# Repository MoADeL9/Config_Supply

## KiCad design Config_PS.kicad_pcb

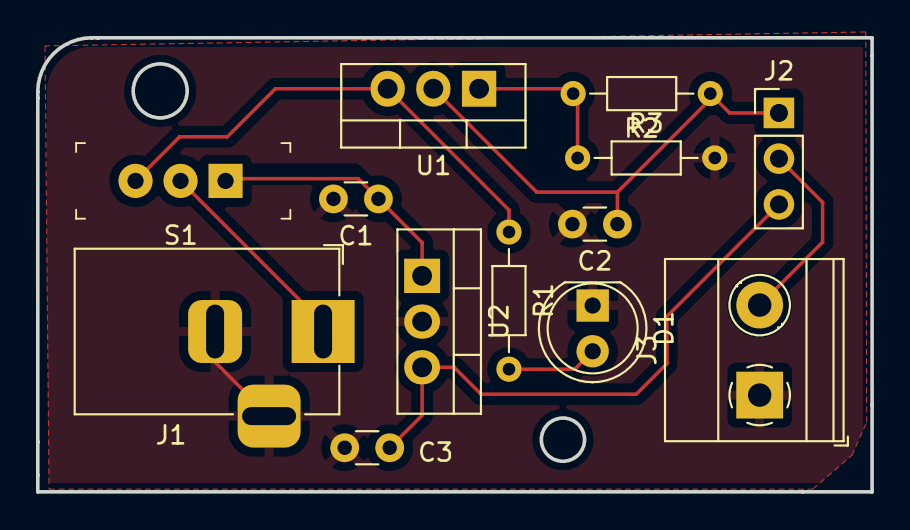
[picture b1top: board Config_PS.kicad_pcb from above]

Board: 2 copper layers, 46.3 x 25.2 mm, 13 parts (0 on the bottom side), 9 nets.

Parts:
C1: 10uf; C_Disc_D3.0mm_W1.6mm_P2.50mm
C2: 1uf; C_Disc_D3.0mm_W1.6mm_P2.50mm
C3: 0.1uf; C_Disc_D3.0mm_W1.6mm_P2.50mm
D1: LED; LED_D5.0mm
J1: Barrel_Jack_Switch; BarrelJack_Horizontal
J2: Conn_01x03_Pin; PinHeader_1x03_P2.54mm_Vertical
J3: Screw_Terminal_01x02; TerminalBlock_Phoenix_MKDS-1,5-2_1x02_P5.00mm_Horizontal
R1, R2: 330; R_Axial_DIN0204_L3.6mm_D1.6mm_P7.62mm_Horizontal
R3: 560; R_Axial_DIN0204_L3.6mm_D1.6mm_P7.62mm_Horizontal
S1: EG1218; Switch_Slide_11.6x4mm_EG1218
U1: LM317_TO-220; TO-220-3_Vertical
U2: LM7805_TO220; TO-220-3_Vertical

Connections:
/3.3V: C2.1, J2.1, R2.1, U1.2 (VO)
/5V: C3.1, J2.3, U2.3 (VO)
/PWR_input: J1.1, S1.2
/PWR_output: J2.2, J3.2
/VIN_3.3: R1.1, S1.3, U1.3 (VI)
/VIN_5: C1.1, S1.1, U2.1 (VI)
GND: C1.2, C2.2, C3.2, D1.1 (K), J1.2, J1.3, J3.1, R3.2, U2.2 (GND)
unnamed: D1.2 (A), R1.2
unnamed: R2.2, R3.1, U1.1 (ADJ)

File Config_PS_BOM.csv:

"Id";"Designator";"Footprint";"Quantity";"Designation";"Supplier and ref";
1;"U2";"TO-220-3_Vertical";1;"LM7805_TO220";;;
2;"C3";"C_Disc_D3.0mm_W1.6mm_P2.50mm";1;"0.1uf";;;
3;"J1";"BarrelJack_Horizontal";1;"Barrel_Jack_Switch";;;
4;"U1";"TO-220-3_Vertical";1;"LM317_TO-220";;;
5;"J2";"PinHeader_1x03_P2.54mm_Vertical";1;"Conn_01x03_Pin";;;
6;"S1";"Switch_Slide_11.6x4mm_EG1218";1;"EG1218";;;
7;"J3";"TerminalBlock_Phoenix_MKDS-1,5-2_1x02_P5.00mm_Horizontal";1;"Screw_Terminal_01x02";;;
8;"D1";"LED_D5.0mm";1;"LED";;;
9;"C2";"C_Disc_D3.0mm_W1.6mm_P2.50mm";1;"1uf";;;
10;"C1";"C_Disc_D3.0mm_W1.6mm_P2.50mm";1;"10uf";;;
11;"R3";"R_Axial_DIN0204_L3.6mm_D1.6mm_P7.62mm_Horizontal";1;"560";;;
12;"R2,R1";"R_Axial_DIN0204_L3.6mm_D1.6mm_P7.62mm_Horizontal";2;"330";;;

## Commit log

2025-05-17 git now tracks the files inside the config_supply
2025-05-17 deleted date in the schematic design
2025-05-17 added custom logo
2025-05-17 added a box
